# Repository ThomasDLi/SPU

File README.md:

# SPU (work in progress)
Sigma Processing Unit: an indelendently driveable 8-bit CPU designed by myself, inspired by the interface used to communicate with the 6502 microprocesser and Ben Eater's 8 bit cpu. I have also written an article on this project! https://thomasdli.notion.site/Designing-An-8-Bit-CPU-Thomas-Li-f7da20de04c84557adcc27d55567141a

(pcb)

(pcb layout)

(zoomed out screenshot of the schematic)

## Specs
- 8 bit address bus for a total of 256 memory locations (including program counter, which starts at address 0, and can also go up to 255)
- 8 bit data bus

- full 8 bit load immediate instructions supported

- 2 general purpose registers
- add/subtraction for ALU with conditional junps for both Zero and Carry flags

- 16 instructions avaliable currently with minimal edits required in order to increase up to 128 instructions
- 16 clock cycles required for each instruction

- R/W flag for memory

- support for external I/O

- turing complete

- maximum clock speed of idfk

### instruction set

- still writing firmware

## todo

- write firmware
- design a VIA for the processor for I/O

## downloading design

This CPU was designed using 74LS series ICs from Texas Instruments, and was made using Autodesk Eagle.

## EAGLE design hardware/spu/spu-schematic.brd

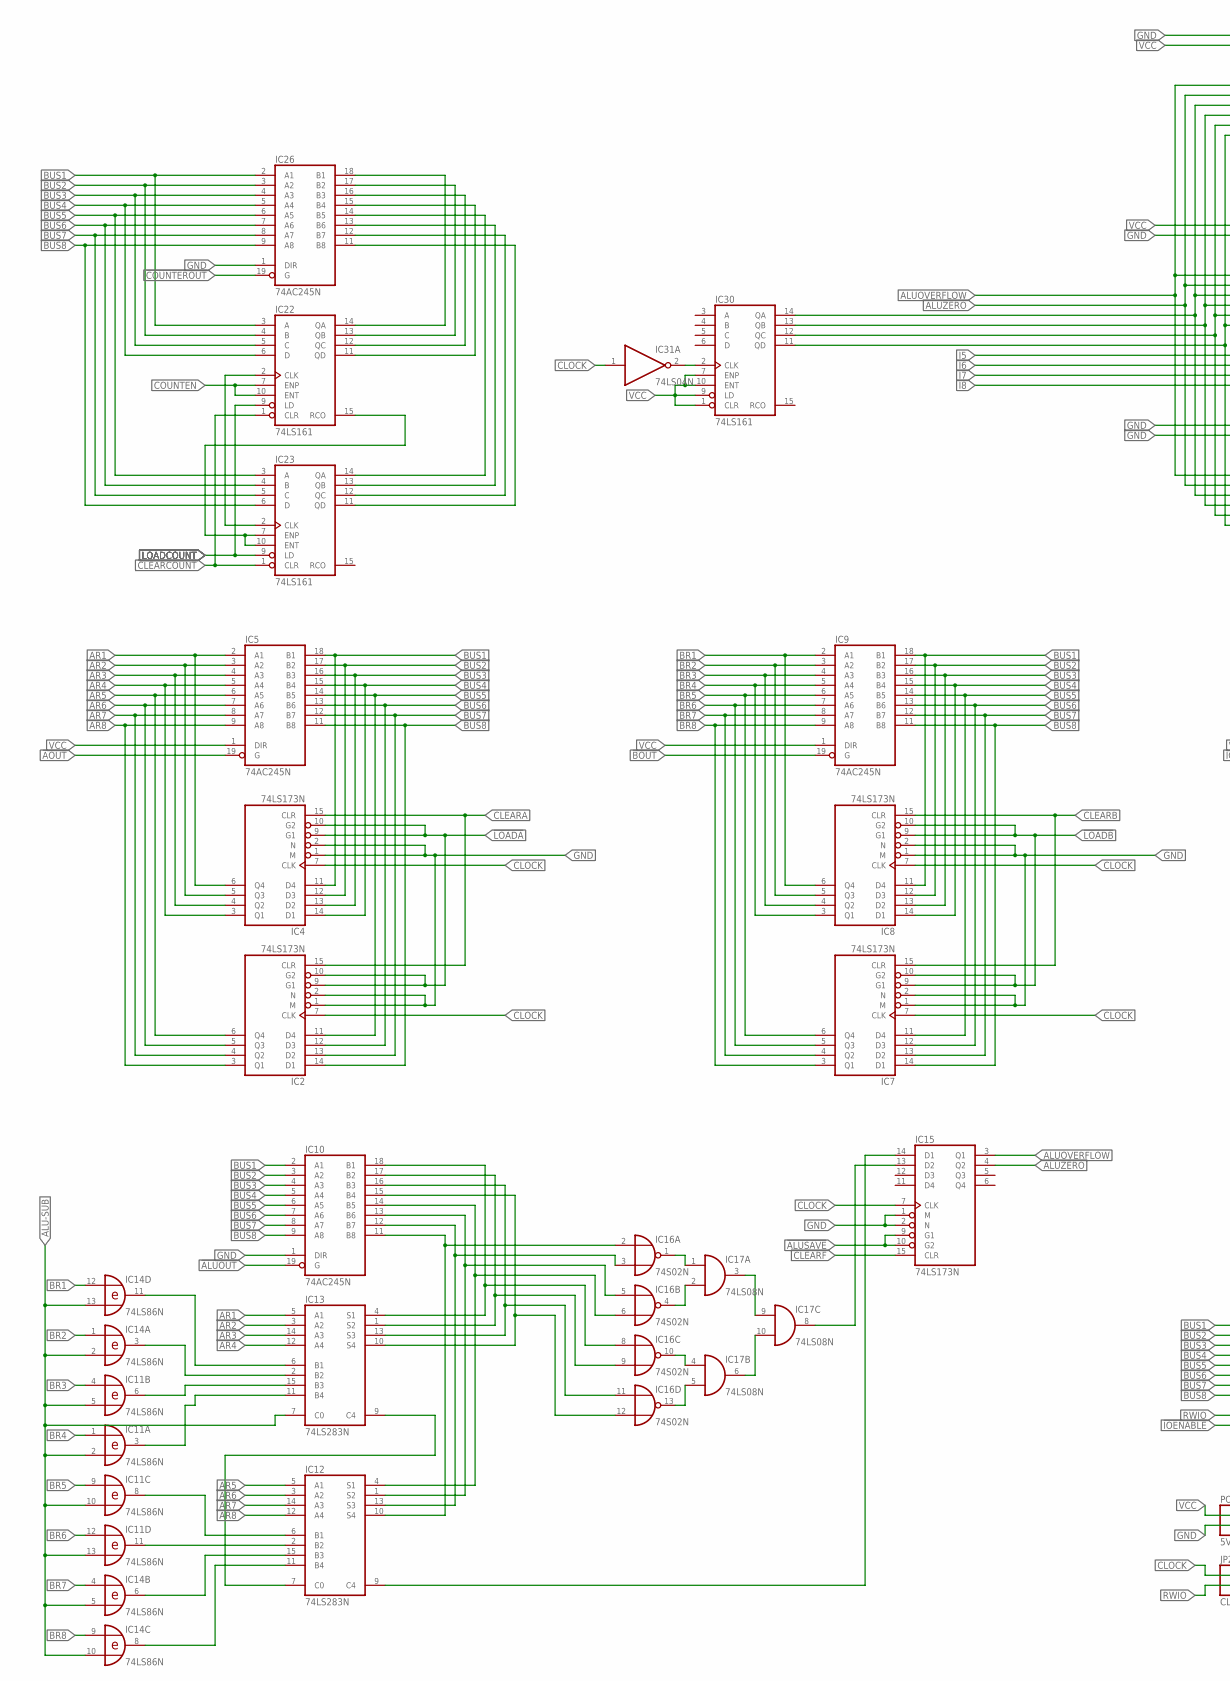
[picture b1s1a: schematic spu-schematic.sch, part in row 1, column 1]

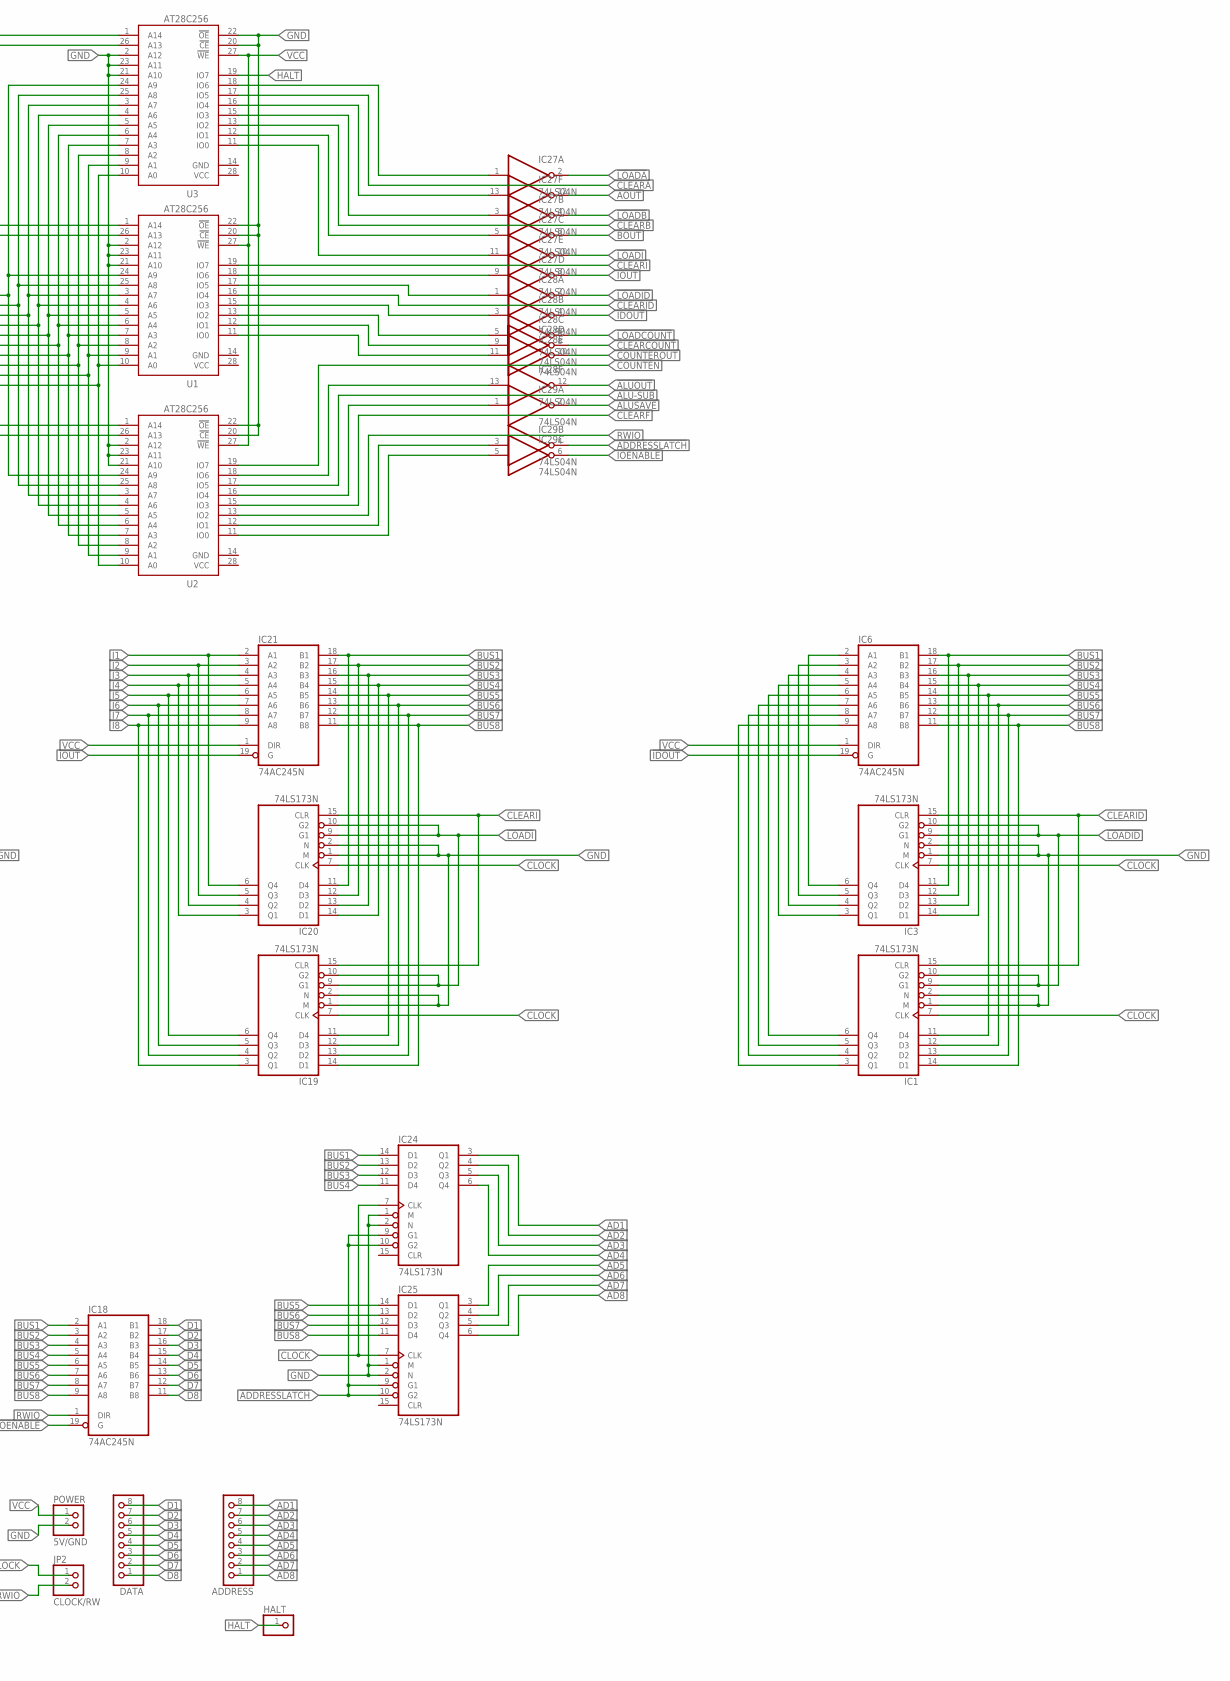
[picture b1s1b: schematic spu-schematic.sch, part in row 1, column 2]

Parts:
ADDRESS: PINHD-1X8; 1X08
DATA: PINHD-1X8; 1X08
HALT: PINHD-1X1; 1X01
IC1, IC2, IC3, IC4, IC7, IC8, IC15, IC19, IC20, IC24, IC25: 74LS173N; DIL16
IC5, IC6, IC9, IC10, IC18, IC21, IC26: 74AC245N; DIL20
IC11, IC14: 74LS86N; DIL14
IC12, IC13: 74LS283N; DIL16
IC16: 74S02N; DIL14
IC17: 74LS08N; DIL14
IC22, IC23, IC30: 74LS161; DIL16
IC27, IC28, IC29, IC31: 74LS04N; DIL14
JP2: CLOCK/RW; 1X02
POWER: 5V/GND; 1X02
U1, U2, U3: AT28C256; DIL28-6

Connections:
!ADDRESSLATCH: IC24.9 (G1), IC24.10 (G2), IC25.9 (G1), IC25.10 (G2), IC29.4 (O)
!ALUOUT: IC10.19 (G), IC28.12 (O)
!ALUSAVE: IC15.9 (G1), IC15.10 (G2), IC29.2 (O)
!AOUT: IC5.19 (G), IC27.12 (O)
!BOUT: IC9.19 (G), IC27.6 (O)
!CLEARCOUNT: IC22.1 (CLR), IC23.1 (CLR), IC28.8 (O)
!COUNTEROUT: IC26.19 (G), IC28.10 (O)
!IDOUT: IC6.19 (G), IC28.4 (O)
!IOENABLE: IC18.19 (G), IC29.6 (O)
!IOUT: IC21.19 (G), IC27.8 (O)
!LOADA: IC2.9 (G1), IC2.10 (G2), IC4.9 (G1), IC4.10 (G2), IC27.2 (O)
!LOADB: IC7.9 (G1), IC7.10 (G2), IC8.9 (G1), IC8.10 (G2), IC27.4 (O)
!LOADCOUNT: IC22.9 (LD), IC23.9 (LD), IC28.6 (O)
!LOADI: IC19.9 (G1), IC19.10 (G2), IC20.9 (G1), IC20.10 (G2), IC27.10 (O)
!LOADID: IC1.9 (G1), IC1.10 (G2), IC3.9 (G1), IC3.10 (G2), IC28.2 (O)
AD1: ADDRESS.8, IC24.3 (Q1)
AD2: ADDRESS.7, IC24.4 (Q2)
AD3: ADDRESS.6, IC24.5 (Q3)
AD4: ADDRESS.5, IC24.6 (Q4)
AD5: ADDRESS.4, IC25.3 (Q1)
AD6: ADDRESS.3, IC25.4 (Q2)
AD7: ADDRESS.2, IC25.5 (Q3)
AD8: ADDRESS.1, IC25.6 (Q4)
ALU-SUB: IC11.2 (I1), IC11.5 (I1), IC11.10 (I1), IC11.13 (I1), IC13.7 (C0), IC14.2 (I1), IC14.5 (I1), IC14.10 (I1), IC14.13 (I1), U2.17 (IO5)
ALUOVERFLOW: IC15.3 (Q1), U1.24 (A9), U2.24 (A9), U3.24 (A9)
ALUZERO: IC15.4 (Q2), U1.25 (A8), U2.25 (A8), U3.25 (A8)
AR1: IC4.6 (Q4), IC5.2 (A1), IC13.5 (A1)
AR2: IC4.5 (Q3), IC5.3 (A2), IC13.3 (A2)
AR3: IC4.4 (Q2), IC5.4 (A3), IC13.14 (A3)
AR4: IC4.3 (Q1), IC5.5 (A4), IC13.12 (A4)
AR5: IC2.6 (Q4), IC5.6 (A5), IC12.5 (A1)
AR6: IC2.5 (Q3), IC5.7 (A6), IC12.3 (A2)
AR7: IC2.4 (Q2), IC5.8 (A7), IC12.14 (A3)
AR8: IC2.3 (Q1), IC5.9 (A8), IC12.12 (A4)
BR1: IC8.6 (Q4), IC9.2 (A1), IC14.12 (I0)
BR2: IC8.5 (Q3), IC9.3 (A2), IC14.1 (I0)
BR3: IC8.4 (Q2), IC9.4 (A3), IC11.4 (I0)
BR4: IC8.3 (Q1), IC9.5 (A4), IC11.1 (I0)
BR5: IC7.6 (Q4), IC9.6 (A5), IC11.9 (I0)
BR6: IC7.5 (Q3), IC9.7 (A6), IC11.12 (I0)
BR7: IC7.4 (Q2), IC9.8 (A7), IC14.4 (I0)
BR8: IC7.3 (Q1), IC9.9 (A8), IC14.9 (I0)
BR9: IC3.6 (Q4), IC6.2 (A1)
BR10: IC3.5 (Q3), IC6.3 (A2)
BR11: IC3.4 (Q2), IC6.4 (A3)
BR12: IC3.3 (Q1), IC6.5 (A4)
BR13: IC1.5 (Q3), IC6.7 (A6)
BR14: IC1.6 (Q4), IC6.6 (A5)
BR15: IC1.4 (Q2), IC6.8 (A7)
BR16: IC1.3 (Q1), IC6.9 (A8)
BUS1: IC3.11 (D4), IC4.11 (D4), IC5.18 (B1), IC6.18 (B1), IC8.11 (D4), IC9.18 (B1), IC10.2 (A1), IC18.2 (A1), IC20.11 (D4), IC21.18 (B1), IC22.3 (A), IC24.14 (D1), IC26.2 (A1)
BUS2: IC3.12 (D3), IC4.12 (D3), IC5.17 (B2), IC6.17 (B2), IC8.12 (D3), IC9.17 (B2), IC10.3 (A2), IC18.3 (A2), IC20.12 (D3), IC21.17 (B2), IC22.4 (B), IC24.13 (D2), IC26.3 (A2)
BUS3: IC3.13 (D2), IC4.13 (D2), IC5.16 (B3), IC6.16 (B3), IC8.13 (D2), IC9.16 (B3), IC10.4 (A3), IC18.4 (A3), IC20.13 (D2), IC21.16 (B3), IC22.5 (C), IC24.12 (D3), IC26.4 (A3)
BUS4: IC3.14 (D1), IC4.14 (D1), IC5.15 (B4), IC6.15 (B4), IC8.14 (D1), IC9.15 (B4), IC10.5 (A4), IC18.5 (A4), IC20.14 (D1), IC21.15 (B4), IC22.6 (D), IC24.11 (D4), IC26.5 (A4)
BUS5: IC1.11 (D4), IC2.11 (D4), IC5.14 (B5), IC6.14 (B5), IC7.11 (D4), IC9.14 (B5), IC10.6 (A5), IC18.6 (A5), IC19.11 (D4), IC21.14 (B5), IC23.3 (A), IC25.14 (D1), IC26.6 (A5)
BUS6: IC1.12 (D3), IC2.12 (D3), IC5.13 (B6), IC6.13 (B6), IC7.12 (D3), IC9.13 (B6), IC10.7 (A6), IC18.7 (A6), IC19.12 (D3), IC21.13 (B6), IC23.4 (B), IC25.13 (D2), IC26.7 (A6)
BUS7: IC1.13 (D2), IC2.13 (D2), IC5.12 (B7), IC6.12 (B7), IC7.13 (D2), IC9.12 (B7), IC10.8 (A7), IC18.8 (A7), IC19.13 (D2), IC21.12 (B7), IC23.5 (C), IC25.12 (D3), IC26.8 (A7)
BUS8: IC1.14 (D1), IC2.14 (D1), IC5.11 (B8), IC6.11 (B8), IC7.14 (D1), IC9.11 (B8), IC10.9 (A8), IC18.9 (A8), IC19.14 (D1), IC21.11 (B8), IC23.6 (D), IC25.11 (D4), IC26.9 (A8)
CLEARA: IC2.15 (CLR), IC4.15 (CLR), U3.17 (IO5)
CLEARB: IC7.15 (CLR), IC8.15 (CLR), U3.13 (IO2)
CLEARF: IC15.15 (CLR), U2.15 (IO3)
CLEARI: IC19.15 (CLR), IC20.15 (CLR), U1.19 (IO7)
CLEARID: IC1.15 (CLR), IC3.15 (CLR), U1.16 (IO4)
CLOCK: IC1.7 (CLK), IC2.7 (CLK), IC3.7 (CLK), IC4.7 (CLK), IC7.7 (CLK), IC8.7 (CLK), IC15.7 (CLK), IC19.7 (CLK), IC20.7 (CLK), IC24.7 (CLK), IC25.7 (CLK), IC30.2 (CLK), IC31.1 (I), IC31.2 (O), JP2.1
COUNTEN: IC22.7 (ENP), IC22.10 (ENT), U2.19 (IO7)
D1: DATA.8, IC18.18 (B1)
D2: DATA.7, IC18.17 (B2)
D3: DATA.6, IC18.16 (B3)
D4: DATA.5, IC18.15 (B4)
D5: DATA.4, IC18.14 (B5)
D6: DATA.3, IC18.13 (B6)
D7: DATA.2, IC18.12 (B7)
D8: DATA.1, IC18.11 (B8)
GND: IC1.1 (M), IC1.2 (N), IC1.8 (GND), IC2.1 (M), IC2.2 (N), IC2.8 (GND), IC3.1 (M), IC3.2 (N), IC3.8 (GND), IC4.1 (M), IC4.2 (N), IC4.8 (GND), IC5.10 (GND), IC6.10 (GND), IC7.1 (M), IC7.2 (N), IC7.8 (GND), IC8.1 (M), IC8.2 (N), IC8.8 (GND), IC9.10 (GND), IC10.1 (DIR), IC10.10 (GND), IC11.7 (GND), IC12.8 (GND), IC13.8 (GND), IC14.7 (GND), IC15.1 (M), IC15.2 (N), IC15.8 (GND), IC16.7 (GND), IC17.7 (GND), IC18.10 (GND), IC19.1 (M), IC19.2 (N), IC19.8 (GND), IC20.1 (M), IC20.2 (N), IC20.8 (GND), IC21.10 (GND), IC22.8 (GND), IC23.8 (GND), IC24.1 (M), IC24.2 (N), IC24.8 (GND), IC25.1 (M), IC25.2 (N), IC25.8 (GND), IC26.1 (DIR), IC26.10 (GND), IC27.7 (GND), IC28.7 (GND), IC29.7 (GND), IC30.8 (GND), IC31.7 (GND), POWER.2, U1.2 (A12), U1.20 (!CE), U1.21 (A10), U1.22 (!OE), U1.23 (A11), U1.26 (A13), U2.1 (A14), U2.2 (A12), U2.20 (!CE), U2.21 (A10), U2.22 (!OE), U2.23 (A11), U2.26 (A13), U3.1 (A14), U3.2 (A12), U3.20 (!CE), U3.21 (A10), U3.22 (!OE), U3.23 (A11)
HALT: HALT.1, U3.19 (IO7)
I1: IC20.6 (Q4), IC21.2 (A1)
I2: IC20.5 (Q3), IC21.3 (A2)
I3: IC20.4 (Q2), IC21.4 (A3)
I4: IC20.3 (Q1), IC21.5 (A4)
I5: IC19.6 (Q4), IC21.6 (A5), U1.7 (A3), U2.7 (A3), U3.7 (A3)
I6: IC19.5 (Q3), IC21.7 (A6), U1.8 (A2), U2.8 (A2), U3.8 (A2)
I7: IC19.4 (Q2), IC21.8 (A7), U1.9 (A1), U2.9 (A1), U3.9 (A1)
I8: IC19.3 (Q1), IC21.9 (A8), U1.10 (A0), U2.10 (A0), U3.10 (A0)
unnamed: IC12.7 (C0), IC13.9 (C4)
unnamed: IC12.11 (B4), IC14.8 (O)
unnamed: IC12.9 (C4), IC15.14 (D1)
unnamed: IC10.14 (B5), IC12.4 (S1), IC16.6 (I1)
unnamed: IC10.13 (B6), IC12.1 (S2), IC16.5 (I0)
unnamed: IC13.6 (B1), IC14.11 (O)
unnamed: IC13.2 (B2), IC14.3 (O)
unnamed: IC11.6 (O), IC13.15 (B3)
unnamed: IC11.3 (O), IC13.11 (B4)
unnamed: IC10.18 (B1), IC13.4 (S1), IC16.8 (I0)
unnamed: IC10.17 (B2), IC13.1 (S2), IC16.9 (I1)
unnamed: IC10.16 (B3), IC13.13 (S3), IC16.11 (I0)
unnamed: IC10.15 (B4), IC13.10 (S4), IC16.12 (I1)
unnamed: IC10.12 (B7), IC12.13 (S3), IC16.3 (I1)
unnamed: IC10.11 (B8), IC12.10 (S4), IC16.2 (I0)
unnamed: IC16.1 (O), IC17.1 (I0)
unnamed: IC22.15 (RCO), IC23.7 (ENP), IC23.10 (ENT)
unnamed: IC29.3 (I), U2.12 (IO1)
unnamed: IC22.2 (CLK), IC23.2 (CLK)
unnamed: IC29.5 (I), U2.11 (IO0)
unnamed: IC11.8 (O), IC12.6 (B1)
unnamed: IC11.11 (O), IC12.2 (B2)
unnamed: IC12.15 (B3), IC14.6 (O)
unnamed: IC22.14 (QA), IC26.18 (B1)
unnamed: IC22.13 (QB), IC26.17 (B2)
unnamed: IC16.4 (O), IC17.2 (I1)
unnamed: IC16.10 (O), IC17.4 (I0)
unnamed: IC16.13 (O), IC17.5 (I1)
unnamed: IC17.3 (O), IC17.9 (I0)
unnamed: IC17.6 (O), IC17.10 (I1)
unnamed: IC15.13 (D2), IC17.8 (O)
unnamed: IC22.12 (QC), IC26.16 (B3)
unnamed: IC22.11 (QD), IC26.15 (B4)
unnamed: IC23.14 (QA), IC26.14 (B5)
unnamed: IC23.13 (QB), IC26.13 (B6)
unnamed: IC23.12 (QC), IC26.12 (B7)
unnamed: IC23.11 (QD), IC26.11 (B8)
unnamed: IC29.1 (I), U2.16 (IO4)
unnamed: IC28.13 (I), U2.18 (IO6)
unnamed: IC28.11 (I), U1.11 (IO0)
unnamed: IC28.9 (I), U1.12 (IO1)
unnamed: IC28.5 (I), U1.13 (IO2)
unnamed: IC28.3 (I), U1.15 (IO3)
unnamed: IC28.1 (I), U1.17 (IO5)
unnamed: IC27.9 (I), U1.18 (IO6)
unnamed: IC27.11 (I), U3.11 (IO0)
unnamed: IC27.5 (I), U3.12 (IO1)
unnamed: IC27.3 (I), U3.15 (IO3)
unnamed: IC27.13 (I), U3.16 (IO4)
unnamed: IC27.1 (I), U3.18 (IO6)
unnamed: IC30.14 (QA), U1.3 (A7), U2.3 (A7), U3.3 (A7)
unnamed: IC30.13 (QB), U1.4 (A6), U2.4 (A6), U3.4 (A6)
unnamed: IC30.12 (QC), U1.5 (A5), U2.5 (A5), U3.5 (A5)
unnamed: IC30.11 (QD), U1.6 (A4), U2.6 (A4), U3.6 (A4)
RWIO: IC18.1 (DIR), JP2.2, U2.13 (IO2)
VCC: IC1.16 (VCC), IC2.16 (VCC), IC3.16 (VCC), IC4.16 (VCC), IC5.1 (DIR), IC5.20 (VCC), IC6.1 (DIR), IC6.20 (VCC), IC7.16 (VCC), IC8.16 (VCC), IC9.1 (DIR), IC9.20 (VCC), IC10.20 (VCC), IC11.14 (VCC), IC12.16 (VCC), IC13.16 (VCC), IC14.14 (VCC), IC15.16 (VCC), IC16.14 (VCC), IC17.14 (VCC), IC18.20 (VCC), IC19.16 (VCC), IC20.16 (VCC), IC21.1 (DIR), IC21.20 (VCC), IC22.16 (VCC), IC23.16 (VCC), IC24.16 (VCC), IC25.16 (VCC), IC26.20 (VCC), IC27.14 (VCC), IC28.14 (VCC), IC29.14 (VCC), IC30.1 (CLR), IC30.7 (ENP), IC30.9 (LD), IC30.10 (ENT), IC30.16 (VCC), IC31.14 (VCC), POWER.1, U1.1 (A14), U1.27 (!WE), U2.27 (!WE), U3.26 (A13), U3.27 (!WE)

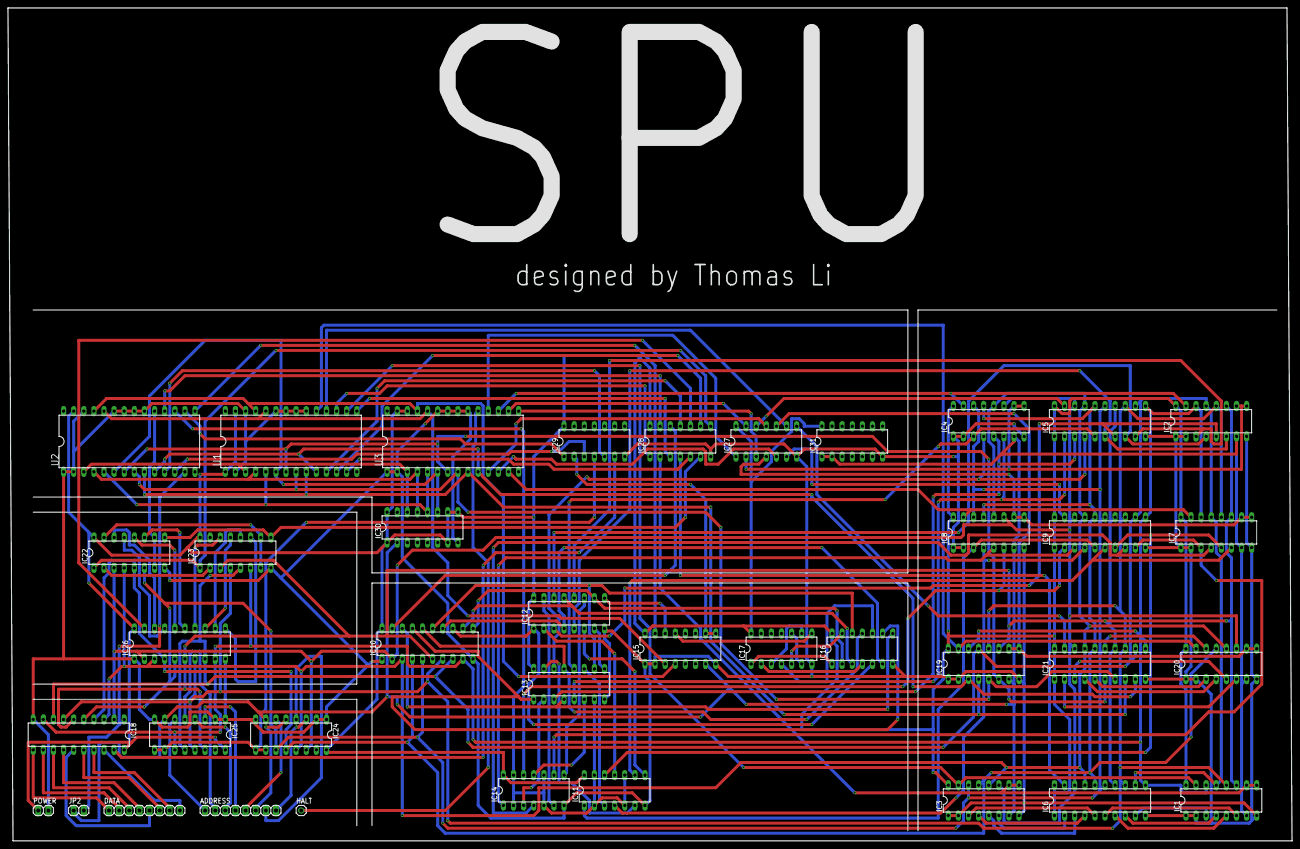
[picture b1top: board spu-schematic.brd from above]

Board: 2 copper layers, 322.6 x 209.2 mm, 39 parts (0 on the bottom side), 139 nets.

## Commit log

2022-08-29 Rename spu-schematic.txt to BOM.txt
2022-08-29 Rename spu-schematic.brd to spu-pcb(unfinished).brd
2022-08-29 Rename BOM.txt to spu-BOM.txt
2022-08-29 Rename spu-BOM.txt to hardware/spu-BOM.txt
2022-08-29 Rename hardware/spu-BOM.txt to hardware/spu/spu-BOM.txt
2022-08-29 Rename spu-schematic.sch to hardware/spu/spu-schematic.sch
2022-08-29 Rename spu-pcb(unfinished).brd to hardware/spu/spu-pcb(unfinished).brd
